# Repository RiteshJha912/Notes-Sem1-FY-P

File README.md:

## SVU - 2023 (P - Physics Group all Theory Notes and Lab Experiments)

This repository has been set up to provide easy access to the notes and lab assignments of First Year Engineering at KJ Somaiya College of Engineering. These resources are from the P group (Physics Group), which are common for all FY students, irrespective of their branch. The goal of this repository is to provide juniors with easy access to essential study materials. [Do not directly copy the codes, as it might get detected by plagiarism checkers]

#### The below table is for easy navigation, but, feel free to explore this Repository yourself, you might find additional important resources.

| **Subject**                        | **Notes/Assignments** | **Lab Assignments/Files** |
|-------------------------------------|-----------------------|---------------------------|
| **Physics**                         | [Notes](https://github.com/RiteshJha912/Notes-Sem1-FY-P/tree/master/Physics/Suren%20Sir) | [Lab Assignments](https://github.com/RiteshJha912/Notes-Sem1-FY-P/tree/master/Physics/PhyLab) |
| **Mechanics**                       | [Notes](https://github.com/RiteshJha912/Notes-Sem1-FY-P/tree/master/Mechanics/ClassNotes/MechNotes) | [Lab Assignments](https://github.com/RiteshJha912/Notes-Sem1-FY-P/tree/master/Mechanics/Lab) |
| **Maths**                           | [Assignments](https://github.com/RiteshJha912/Notes-Sem1-FY-P/tree/master/Maths) | - |
| **Python**                          | -                     | [Lab Assignments](https://github.com/RiteshJha912/Notes-Sem1-FY-P/tree/master/Python/FinalExperiments) |
| **Project Based Learning**          | - | [Lab Assignments](https://github.com/RiteshJha912/Notes-Sem1-FY-P/tree/master/PBL) |
| **Presentation and Comm Skills**    | [Assignments](https://github.com/RiteshJha912/Notes-Sem1-FY-P/tree/master/PBL) | - |
| **Workshop**                        | - | [Files](https://github.com/RiteshJha912/Notes-Sem1-FY-P/tree/master/Workshop) |
| **Question Papers**                 | [ESE Samples](https://github.com/RiteshJha912/Notes-Sem1-FY-P/blob/master/ESEPapers.pdf) | - |

This repository is also open to collaboration. We are looking for contributors who can help expand the resources and improve the variety of notes and assignments available. If you're interested in contributing, feel free to reach out!  
**Drop me a mail at:** ritesh.exe@proton.me

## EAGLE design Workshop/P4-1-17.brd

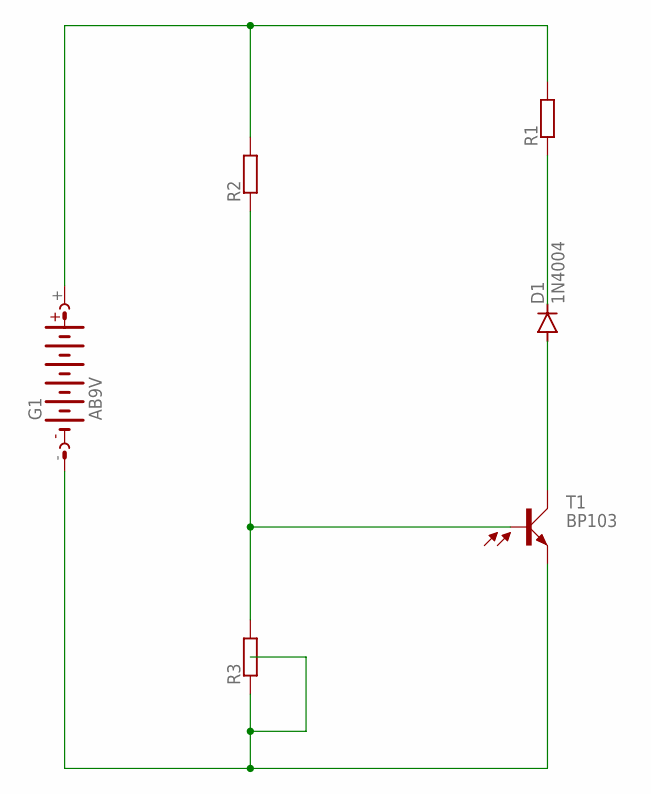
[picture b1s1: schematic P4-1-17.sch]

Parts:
D1: 1N4004; DO41-10
G1: AB9V
R1, R2, R3: BVS
T1: BP103

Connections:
unnamed: G1.-, R3.2, T1.E
unnamed: R2.2, R3.1, T1.B
unnamed: D1.A, T1.C
unnamed: D1.C, R1.2
unnamed: G1.+, R1.1, R2.1

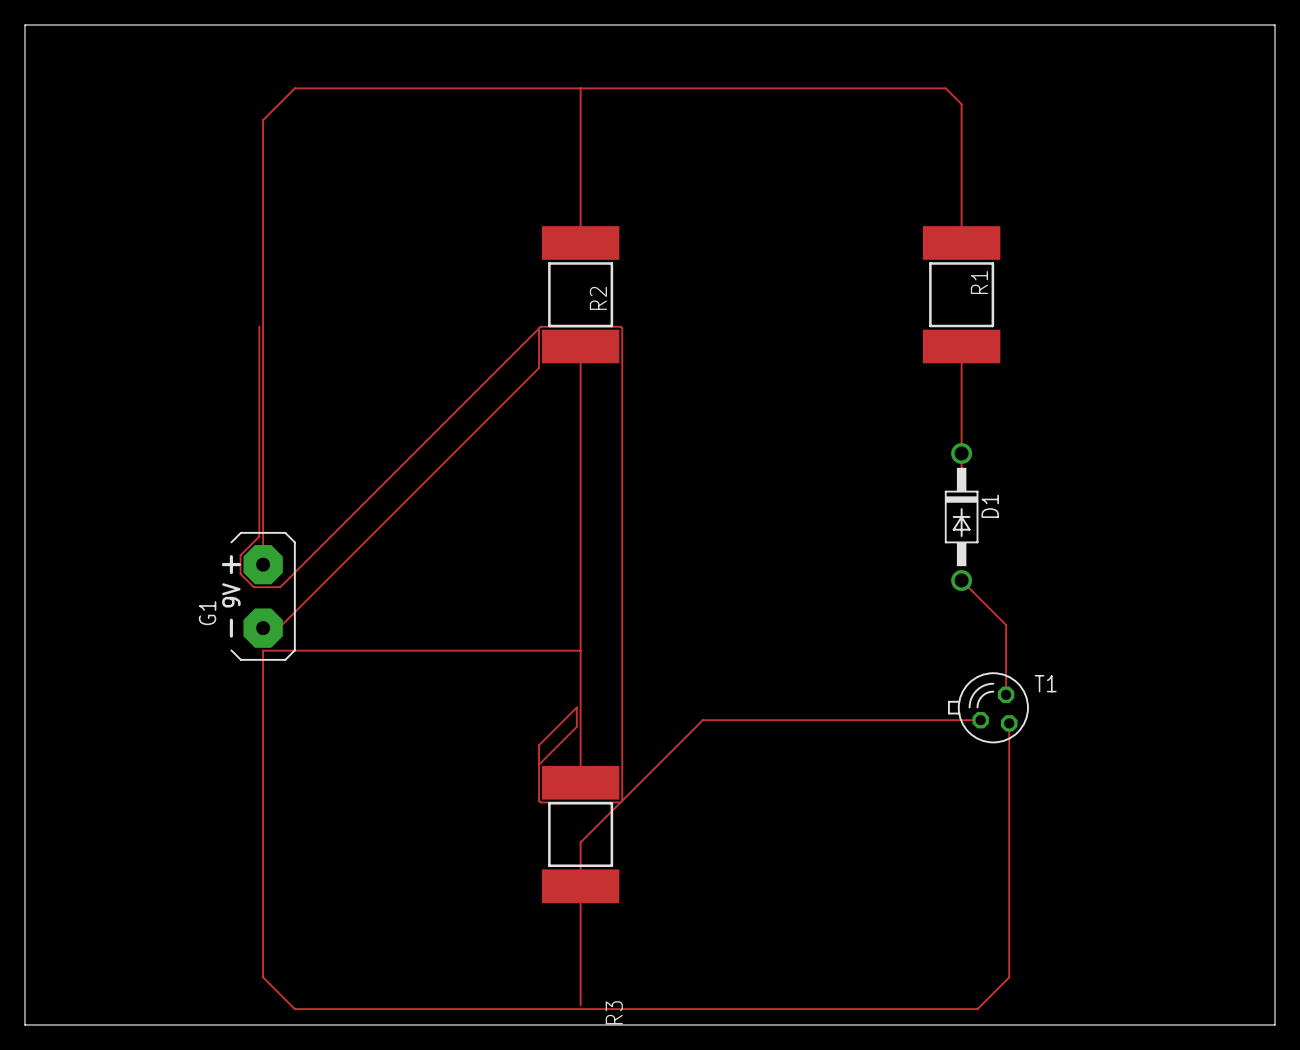
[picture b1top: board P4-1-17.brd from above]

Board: 2 copper layers, 100.0 x 80.0 mm, 6 parts (0 on the bottom side), 5 nets.

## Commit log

2024-10-01 first
